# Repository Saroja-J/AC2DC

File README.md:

# ⚡ AC to DC Converter

A simple **AC to DC Converter** designed in **KiCad** using a bridge rectifier, filter capacitor, and LED indicator. The circuit converts AC voltage from a transformer secondary into a smooth DC output suitable for low-power electronic applications.

---

## ⚙️ How It Works

1. AC voltage is supplied from the transformer secondary.
2. Four **1N4007** diodes form a full-wave bridge rectifier.
3. The filter capacitor smooths the rectified voltage.
4. The LED indicates that power is available.
5. The DC output is provided through the output connector.

---

## ✨ Features

✔️ Simple and beginner-friendly design

✔️ Full-wave bridge rectification

✔️ Reduced ripple using filter capacitor

✔️ LED power indication

✔️ Designed using KiCad

---

## 🛠️ Components Used

- 4 × 1N4007 Diodes
- 1000 µF Capacitor
- 10 kΩ Resistor
- 2.2 kΩ Resistor
- LED
- Input & Output Connectors

---

## 📷 Schematic

---

## 📄 License

This project is shared for educational and learning purposes.

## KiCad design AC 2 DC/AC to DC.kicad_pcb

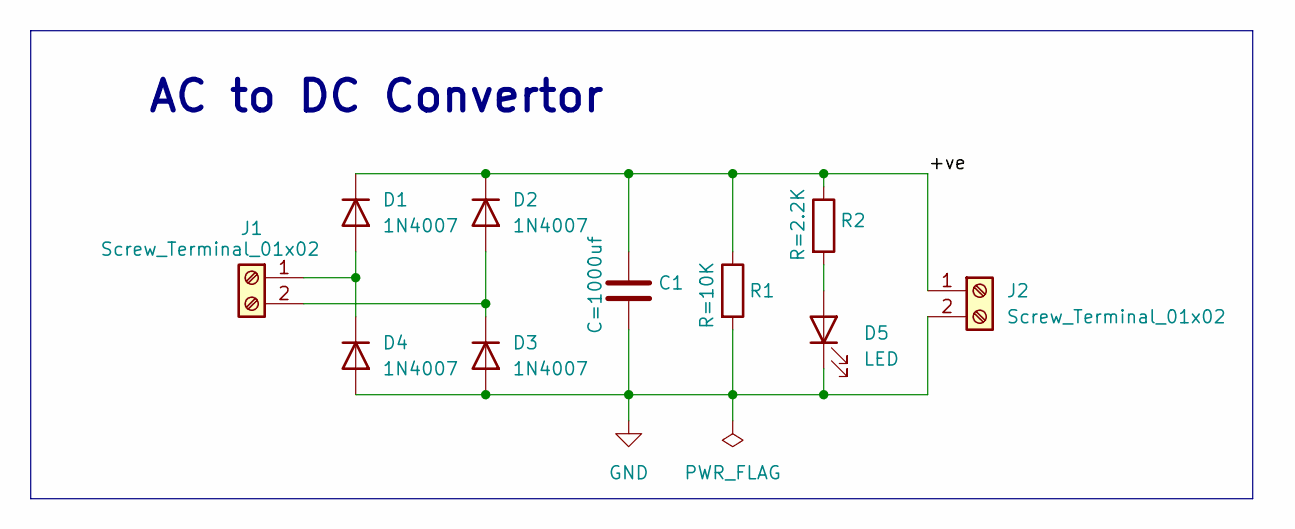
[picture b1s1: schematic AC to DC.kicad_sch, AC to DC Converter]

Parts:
C1: C=1000uf; C_Radial_D8.0mm_H11.5mm_P3.50mm
D1, D2, D3, D4: 1N4007; D_DO-41_SOD81_P10.16mm_Horizontal
D5: LED; LED_D5.0mm
J1, J2: Screw_Terminal_01x02; TerminalBlock_Phoenix_MKDS-1,5-2-5.08_1x02_P5.08mm_Horizont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
R1: R=10K; R_Axial_DIN0204_L3.6mm_D1.6mm_P7.62mm_Horizontal
R2: R=2.2K; R_Axial_DIN0204_L3.6mm_D1.6mm_P7.62mm_Horizontal

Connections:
/+ve: C1.1, D1.1 (K), D2.1 (K), J2.1, R1.1, R2.1
GND: C1.2, D3.2 (A), D4.2 (A), D5.1 (K), J2.2, R1.2
unnamed: D1.2 (A), D4.1 (K), J1.1
unnamed: D2.2 (A), D3.1 (K), J1.2
unnamed: D5.2 (A), R2.2

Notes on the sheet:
AC to DC Convertor

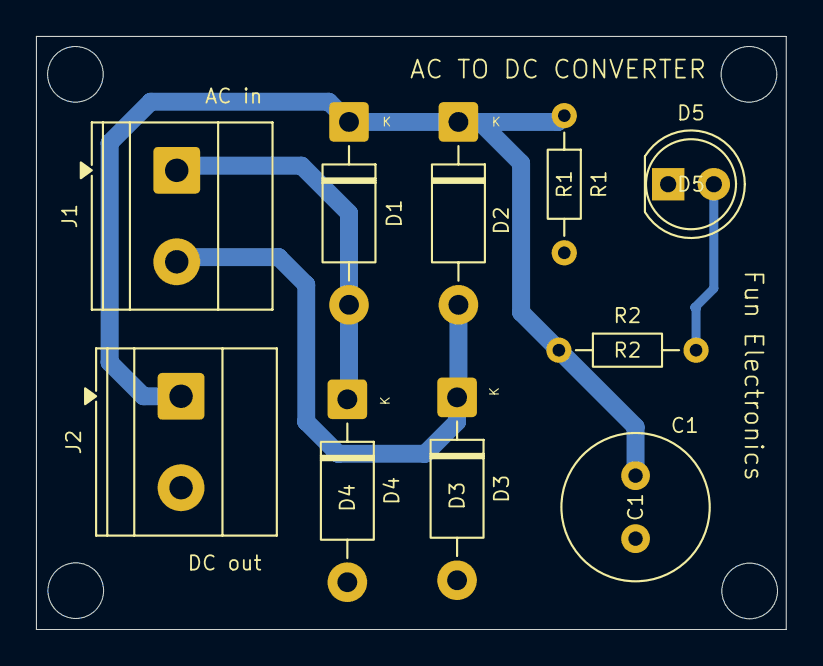
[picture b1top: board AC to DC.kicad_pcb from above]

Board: 2 copper layers, 41.7 x 32.9 mm, 10 parts (0 on the bottom side), 5 nets.
